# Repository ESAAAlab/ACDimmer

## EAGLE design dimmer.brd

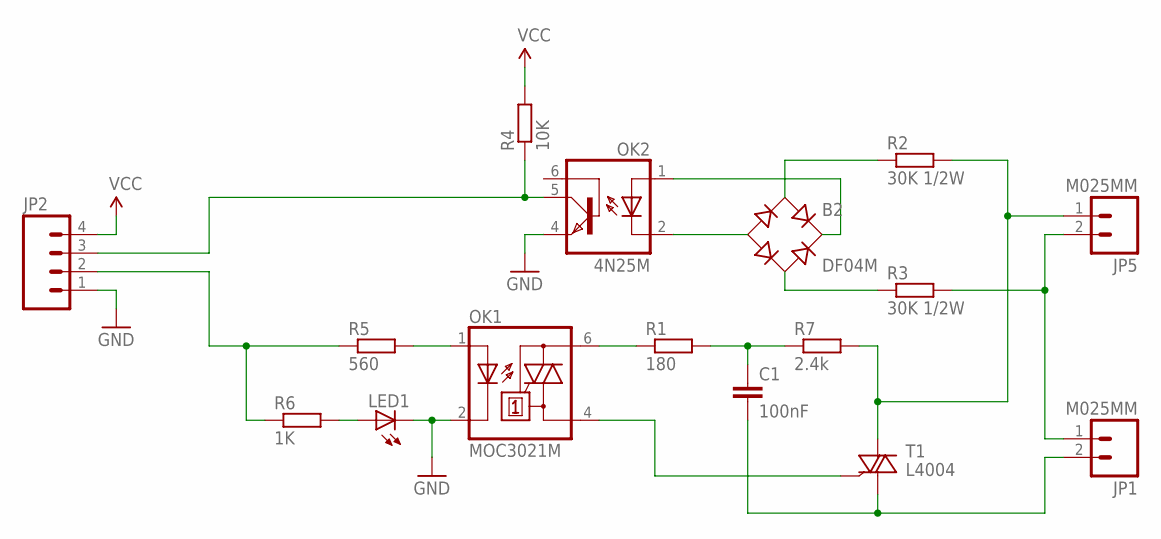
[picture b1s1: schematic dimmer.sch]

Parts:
B2: DF04M; B-DIL
C1: 100nF; C050-025X075
JP1, JP5: M025MM; SCREWTERMINAL-5MM-2
JP2: M04LOCK; 1X04_LOCK
LED1: LED5MM
OK1: MOC3021M; DIL06
OK2: 4N25M; DIL06
R1: 180; 0309/12
R2, R3: 30K 1/2W; 0309/12
R4: 10K; 0207/2V
R5: 560; 0207/2V
R6: 1K; 0207/2V
R7: 2.4k; 0309/12
T1: L4004; TO220AB

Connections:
GND: JP2.1, LED1.K (C), OK1.2 (C), OK2.4 (EMI)
unnamed: B2.+, OK2.1 (A)
unnamed: B2.-, OK2.2 (C)
unnamed: B2.AC1, R2.1
unnamed: B2.AC2, R3.1
unnamed: C1.1, R1.2, R7.1
unnamed: OK1.6 (A2), R1.1
unnamed: JP5.1, R2.2, R7.2, T1.2 (A2)
unnamed: JP1.1, JP5.2, R3.2
unnamed: C1.2, JP1.2, T1.1 (A1)
unnamed: JP2.3, OK2.5 (COL), R4.1
unnamed: JP2.2, R5.1, R6.1
unnamed: OK1.1 (A), R5.2
unnamed: LED1.A, R6.2
unnamed: OK1.4 (A1), T1.3 (G)
VCC: JP2.4, R4.2

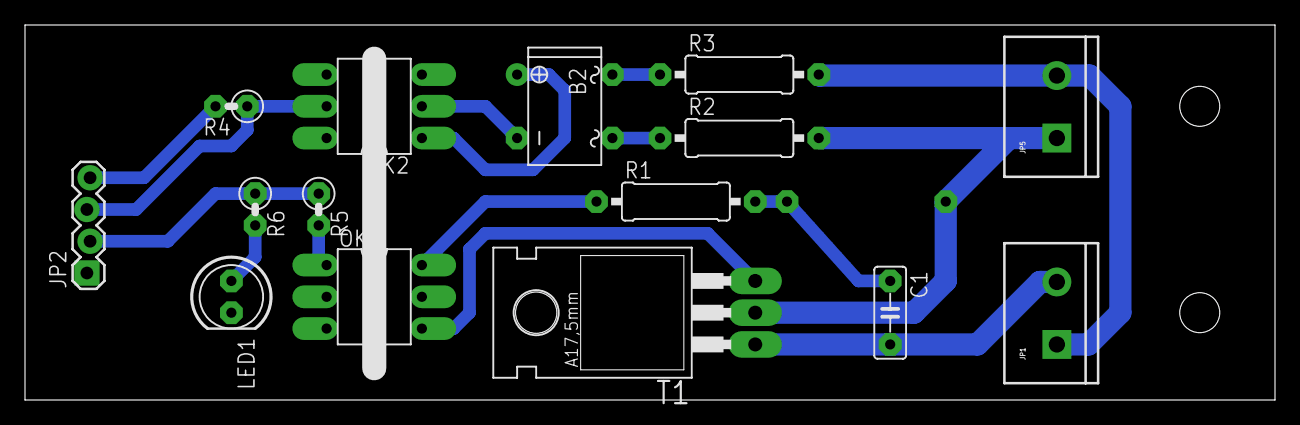
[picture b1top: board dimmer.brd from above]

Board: 2 copper layers, 100.0 x 30.0 mm, 16 parts (1 on the bottom side), 16 nets.

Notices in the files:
parts and their libraries:
SparkFun-Connectors: Licensing: CC v3.0 Share-Alike You are welcome to use this library for commercial purposes.
